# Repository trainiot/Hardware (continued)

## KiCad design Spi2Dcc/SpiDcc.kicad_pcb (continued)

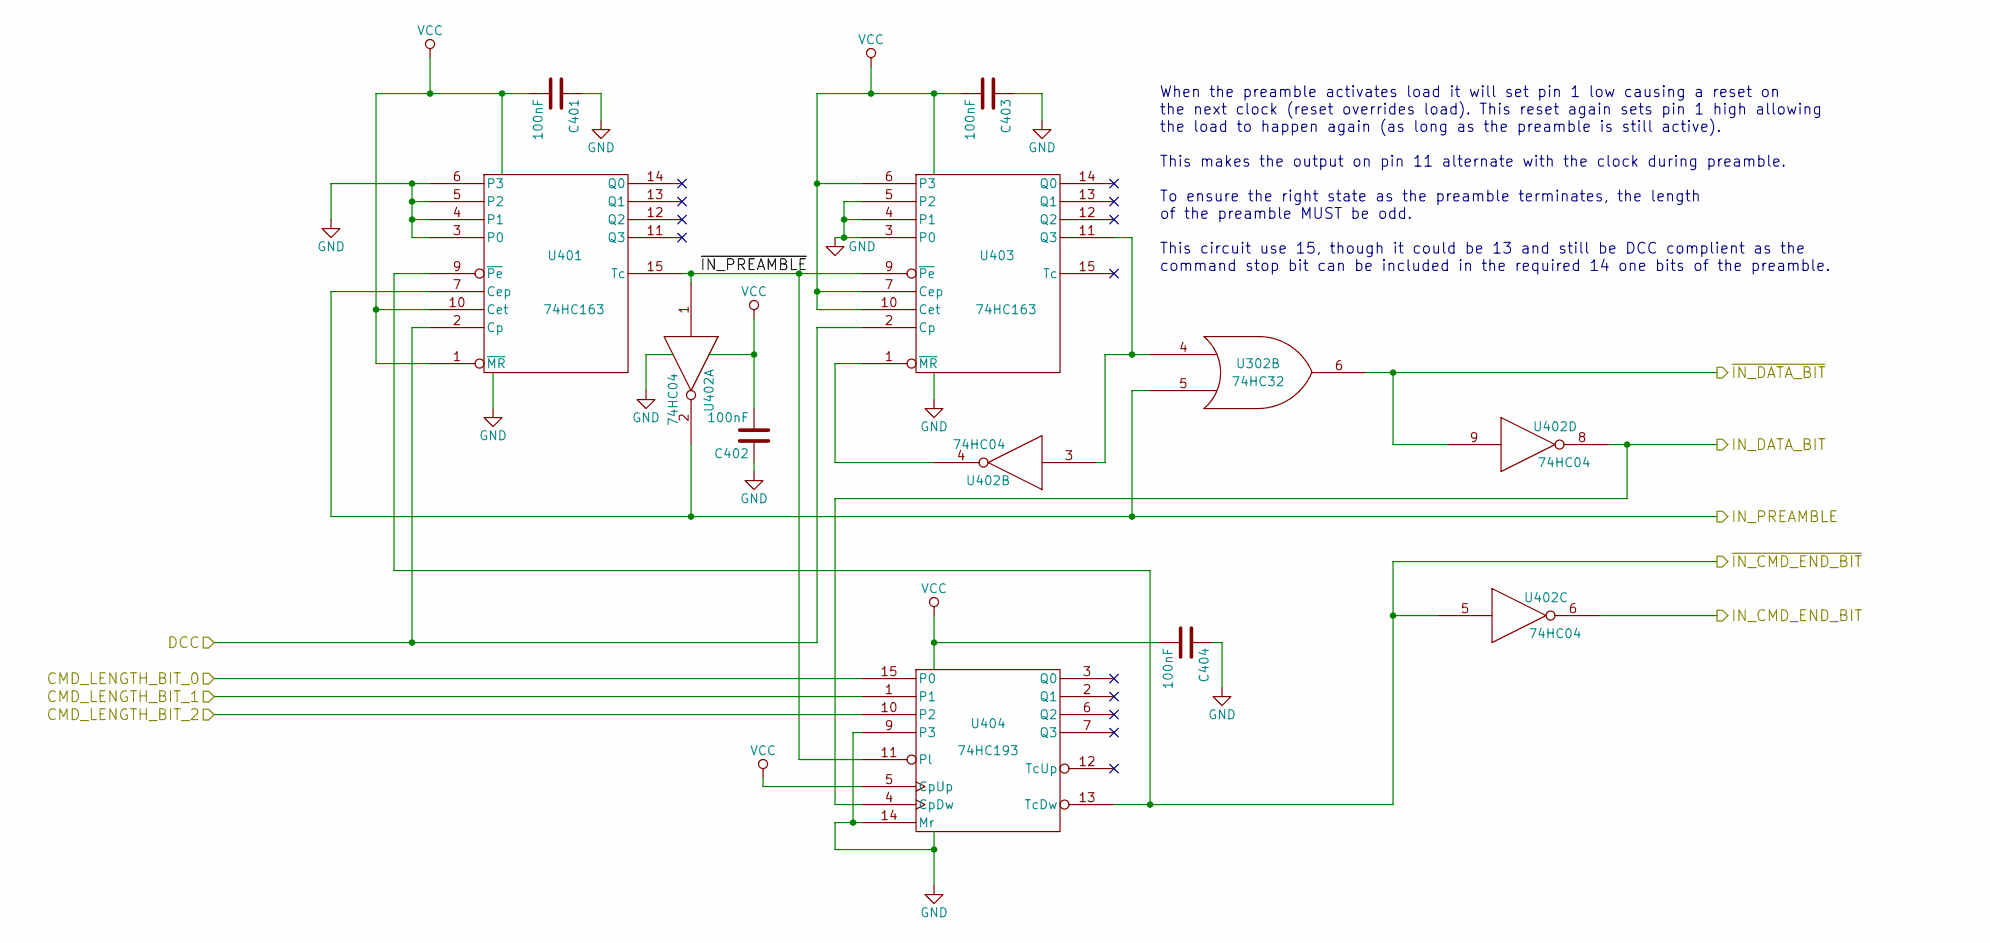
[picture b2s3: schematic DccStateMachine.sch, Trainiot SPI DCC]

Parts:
C401, C402, C403, C404: 100nF; C_0603
U302: 74HC32; SOIC-14_N
U401, U403: 74HC163; SO-16-N
U402: 74HC04; SOIC-14_N
U404: 74HC193; SO-16-N

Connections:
/Booster Connectors/DCC: U401.2 (Cp), U403.2 (Cp); also elsewhere on the board
/Command Register/CMD_LENGTH_BIT_0: U404.15 (P0); also elsewhere on the board
/Command Register/CMD_LENGTH_BIT_1: U404.1; also elsewhere on the board
/Command Register/CMD_LENGTH_BIT_2: U404.10 (P2); also elsewhere on the board
/Command Register/IN_CMD_END_BIT: U402.6; also elsewhere on the board
/Command Register/~IN_CMD_END_BIT~: U401.9 (~Pe), U402.5, U404.13 (TcDw); also elsewhere on the board
/Command Register/~IN_DATA_BIT~: U302.6, U402.9; also elsewhere on the board
/DCC Generator/IN_DATA_BIT: U402.8, U404.4 (CpDw); also elsewhere on the board
/DCC Generator/IN_PREAMBLE: U302.5, U401.7 (Cep), U402.2; also elsewhere on the board
/DCC State Machine/~IN_PREAMBLE~: U401.15 (Tc), U402.1, U403.9 (~Pe), U404.11 (Pl)
GND: C401.1, C402.1, C403.1, C404.1, U302.7 (GND), U401.3 (P0), U401.4 (P1), U401.5 (P2), U401.6 (P3), U401.8 (GND), U402.7 (GND), U403.3 (P0), U403.4 (P1), U403.5 (P2), U403.8 (GND), U404.8 (GND), U404.9 (P3), U404.14 (Mr); also elsewhere on the board
unnamed: U302.4, U402.3, U403.11 (Q3)
unnamed: U402.4, U403.1 (~MR)
VCC: C401.2, C402.2, C403.2, C404.2, U302.14 (VCC), U401.1 (~MR), U401.10 (Cet), U401.16 (VCC), U402.14 (VCC), U403.6 (P3), U403.7 (Cep), U403.10 (Cet), U403.16 (VCC), U404.5 (CpUp), U404.16 (VCC); also elsewhere on the board

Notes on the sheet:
When the preamble activates load it will set pin 1 low causing a reset on the next clock (reset overrides load). This reset again sets pin 1 high allowing the load to happen again (as long as the preamble is still active). This makes the output on pin 11 alternate with the clock during preamble. To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

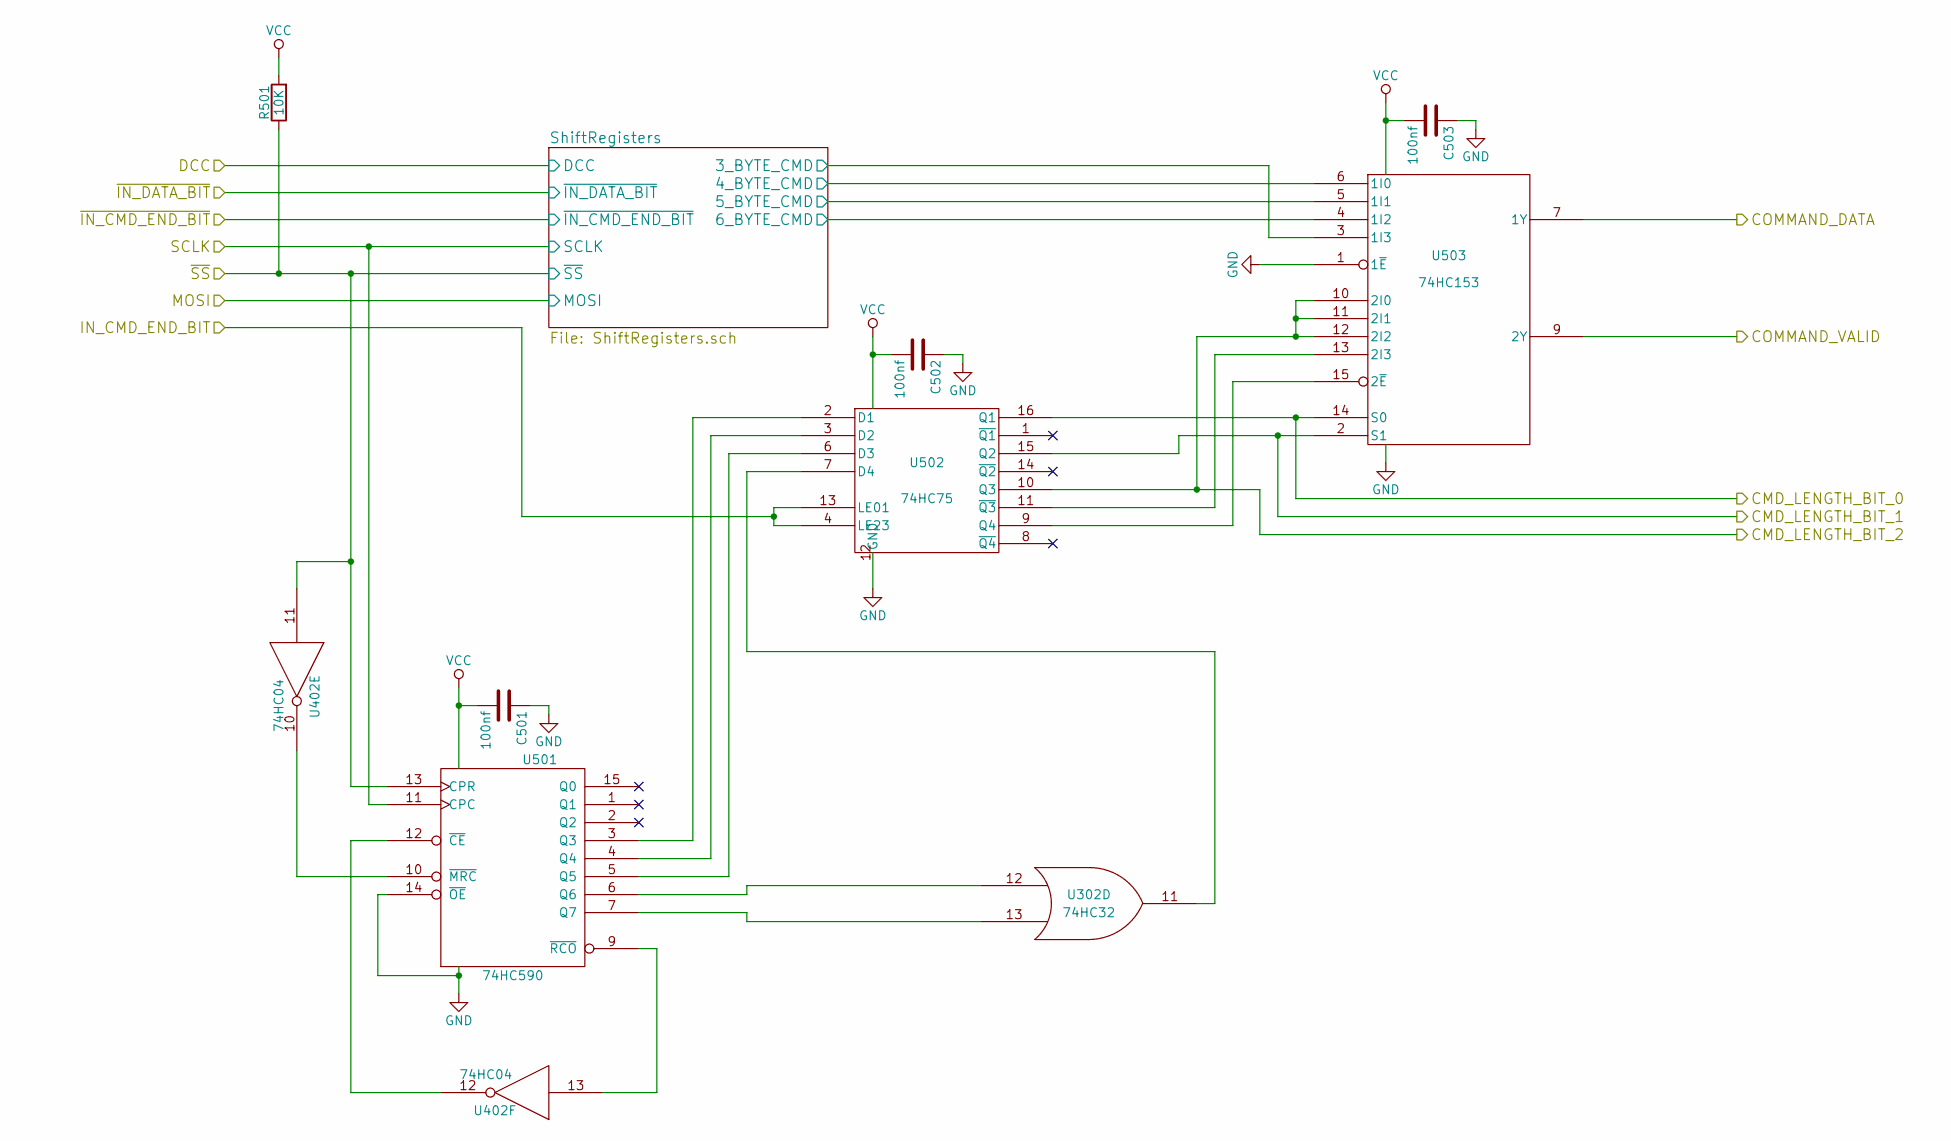
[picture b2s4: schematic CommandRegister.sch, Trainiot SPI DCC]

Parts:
C501, C502, C503: 100nf; C_0603
R501: 10K; R_0603
U302: 74HC32; SOIC-14_N
U402: 74HC04; SOIC-14_N
U501: 74HC590; SO-16-N
U502: 74HC75; SO-16-N
U503: 74HC153; SO-16-N

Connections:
/Command Register/CMD_LENGTH_BIT_0: U502.16 (Q1), U503.14 (S0); also elsewhere on the board
/Command Register/CMD_LENGTH_BIT_1: U502.15 (Q2), U503.2 (S1); also elsewhere on the board
/Command Register/CMD_LENGTH_BIT_2: U502.10 (Q3), U503.10 (2I0), U503.11 (2I1), U503.12 (2I2); also elsewhere on the board
/Command Register/COMMAND_DATA: U503.7 (1Y); also elsewhere on the board
/Command Register/COMMAND_VALID: U503.9 (2Y); also elsewhere on the board
/Command Register/IN_CMD_END_BIT: U502.4 (LE23), U502.13 (LE01); also elsewhere on the board
/Command Register/SCLK: U501.11 (CPC); also elsewhere on the board
/Command Register/ShiftRegisters/3_BYTE_CMD: U503.3 (1I3); also elsewhere on the board
/Command Register/ShiftRegisters/4_BYTE_CMD: U503.6 (1I0); also elsewhere on the board
/Command Register/ShiftRegisters/5_BYTE_CMD: U503.5 (1I1); also elsewhere on the board
/Command Register/ShiftRegisters/6_BYTE_CMD: U503.4 (1I2); also elsewhere on the board
/Command Register/~SS~: R501.1, U402.11, U501.13 (CPR); also elsewhere on the board
GND: C501.1, C502.1, C503.1, U302.7 (GND), U402.7 (GND), U501.8 (GND), U501.14 (~OE), U502.12 (GND), U503.1 (1~E~), U503.8 (GND); also elsewhere on the board
unnamed: U302.11, U502.7 (D4)
unnamed: U302.12, U501.6 (Q6)
unnamed: U302.13, U501.7 (Q7)
unnamed: U402.10, U501.10 (~MRC)
unnamed: U402.12, U501.12 (~CE)
unnamed: U402.13, U501.9 (~RCO)
unnamed: U501.3 (Q3), U502.2 (D1)
unnamed: U501.4 (Q4), U502.3 (D2)
unnamed: U501.5 (Q5), U502.6 (D3)
unnamed: U502.9 (Q4), U503.15 (2~E~)
unnamed: U502.11 (~Q3), U503.13 (2I3)
VCC: C501.2, C502.2, C503.2, R501.2, U302.14 (VCC), U402.14 (VCC), U501.16 (VCC), U502.5 (VCC), U503.16 (VCC); also elsewhere on the board

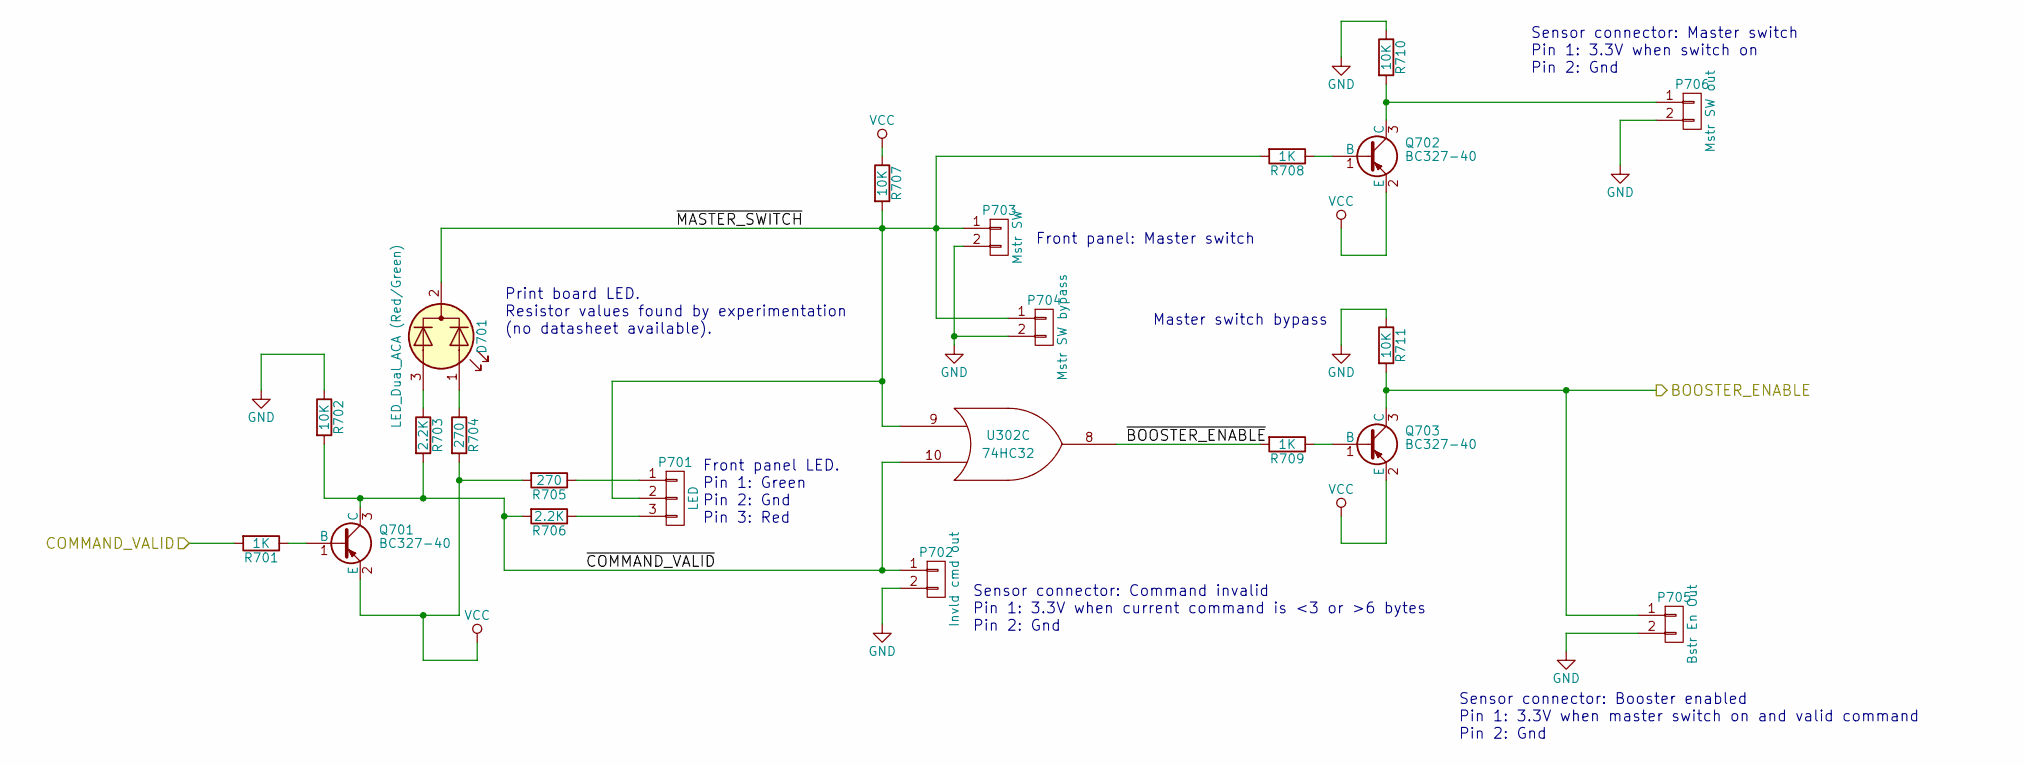
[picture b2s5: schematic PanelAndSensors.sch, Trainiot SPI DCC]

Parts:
D701: LED_Dual_ACA (Red/Green); LED_D3.0mm-3
P701: LED; JST_XH_B03B-XH-A_03x2.50mm_Straight
P702: Invld cmd out; JST_XH_B02B-XH-A_02x2.50mm_Straight
P703: Mstr SW; JST_XH_B02B-XH-A_02x2.50mm_Straight
P704: Mstr SW bypass; Pin_Header_Straight_1x02_Pitch2.54mm
P705: Bstr En Out; JST_XH_B02B-XH-A_02x2.50mm_Straight
P706: Mstr SW out; JST_XH_B02B-XH-A_02x2.50mm_Straight
Q701, Q702, Q703: BC327-40; SOT-23
R701, R708, R709: 1K; R_0603
R702, R707, R710, R711: 10K; R_0603
R703, R706: 2.2K; R_0603
R704, R705: 270; R_0603
U302: 74HC32; SOIC-14_N

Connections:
/Booster Connectors/BOOSTER_ENABLE: P705.1, Q703.3 (C), R711.2; also elsewhere on the board
/Command Register/COMMAND_VALID: R701.2; also elsewhere on the board
/Panel and Sensors/~BOOSTER_ENABLE: R709.2, U302.8
/Panel and Sensors/~COMMAND_VALID: P702.1, Q701.3 (C), R702.2, R703.2, R706.2, U302.10
/Panel and Sensors/~MASTER_SWITCH: D701.2 (K), P701.2, P703.1, P704.1, R707.2, R708.2, U302.9
GND: P702.2, P703.2, P704.2, P705.2, P706.2, R702.1, R710.1, R711.1, U302.7 (GND); also elsewhere on the board
unnamed: D701.1 (A1), R704.1
unnamed: D701.3 (A2), R703.1
unnamed: P701.1, R705.1
unnamed: P701.3, R706.1
unnamed: P706.1, Q702.3 (C), R710.2
unnamed: Q701.1 (B), R701.1
unnamed: Q702.1 (B), R708.1
unnamed: Q703.1 (B), R709.1
VCC: Q701.2 (E), Q702.2 (E), Q703.2 (E), R704.2, R705.2, R707.1, U302.14 (VCC); also elsewhere on the board

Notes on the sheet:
Print board LED. Resistor values found by experimentation (no datasheet available).
Front panel LED. Pin 1: Green Pin 2: Gnd Pin 3: Red
Sensor connector: Booster enabled Pin 1: 3.3V when master switch on and valid command Pin 2: Gnd
Sensor connector: Master switch Pin 1: 3.3V when switch on Pin 2: Gnd
Sensor connector: Command invalid Pin 1: 3.3V when current command is <3 or >6 bytes Pin 2: Gnd
Front panel: Master switch
Master switch bypass

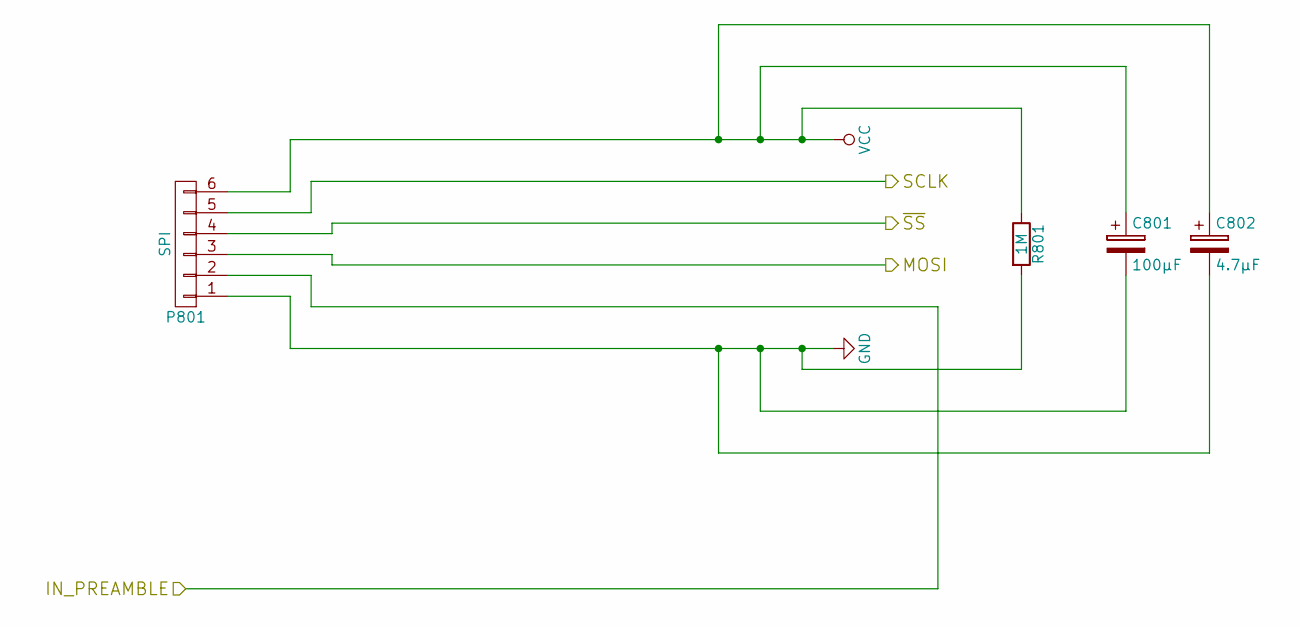
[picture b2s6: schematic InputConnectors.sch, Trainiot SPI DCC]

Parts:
C801: 100μF; CP_Radial_D6.3mm_P2.50mm
C802: 4.7μF; CP_Radial_D5.0mm_P2.00mm
P801: SPI; JST_XH_B06B-XH-A_06x2.50mm_Straight
R801: 1M; R_0603

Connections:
/Command Register/MOSI: P801.3; also elsewhere on the board
/Command Register/SCLK: P801.5; also elsewhere on the board
/Command Register/~SS~: P801.4; also elsewhere on the board
/DCC Generator/IN_PREAMBLE: P801.2; also elsewhere on the board
GND: C801.2, C802.2, P801.1, R801.2; also elsewhere on the board
VCC: C801.1, C802.1, P801.6, R801.1; also elsewhere on the board

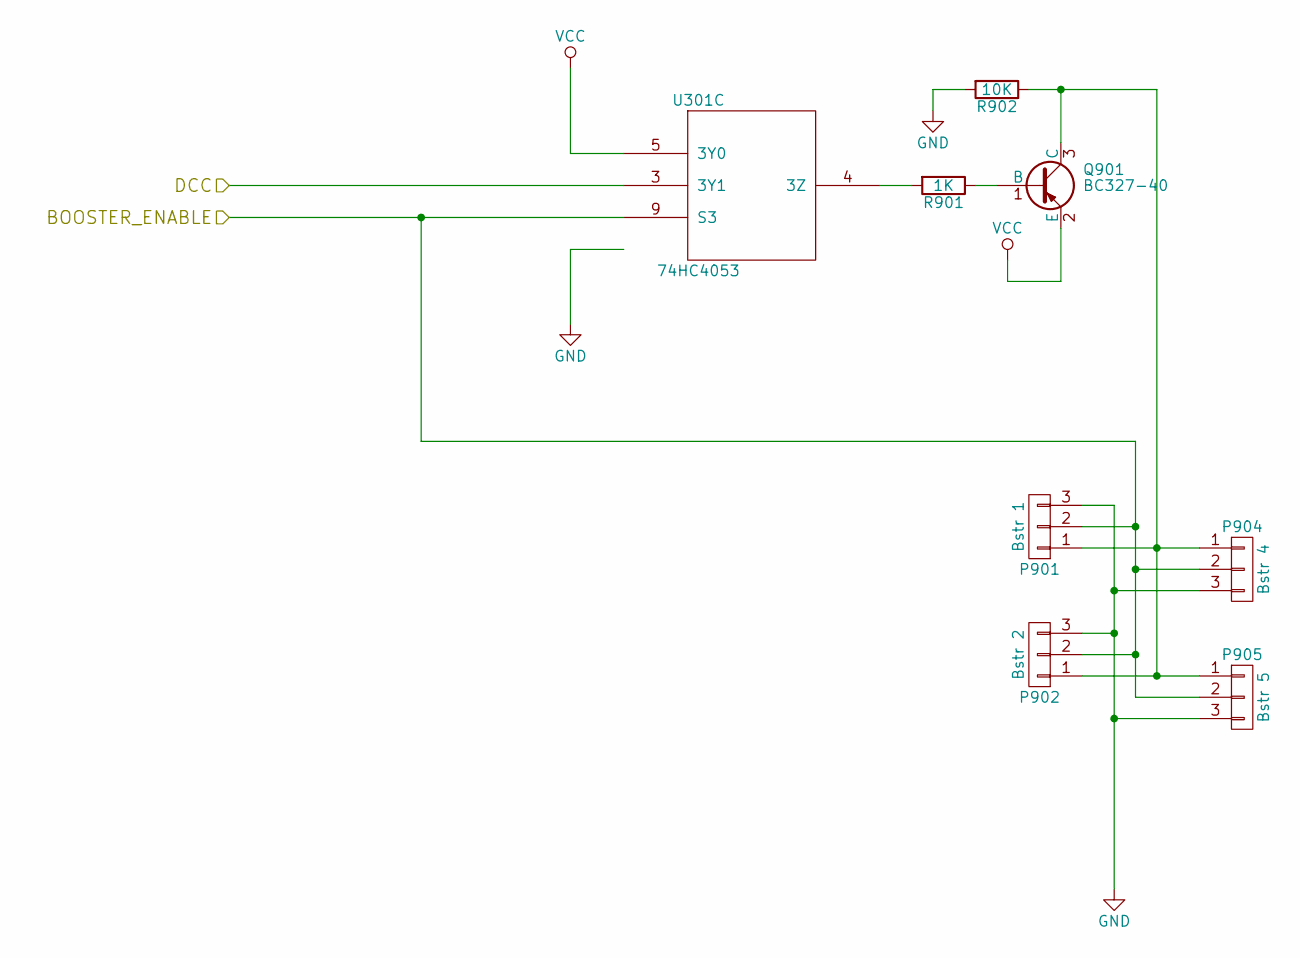
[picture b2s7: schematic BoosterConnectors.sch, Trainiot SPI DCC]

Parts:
P901: Bstr 1; JST_XH_B03B-XH-A_03x2.50mm_Straight
P902: Bstr 2; JST_XH_B03B-XH-A_03x2.50mm_Straight
P904: Bstr 4; JST_XH_B03B-XH-A_03x2.50mm_Straight
P905: Bstr 5; JST_XH_B03B-XH-A_03x2.50mm_Straight
Q901: BC327-40; SOT-23
R901: 1K; R_0603
R902: 10K; R_0603
U301: 74HC4053; SO-16-N

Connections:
/Booster Connectors/BOOSTER_ENABLE: P901.2, P902.2, P904.2, P905.2, U301.9 (S3); also elsewhere on the board
/Booster Connectors/DCC: U301.3 (3Y1); also elsewhere on the board
GND: P901.3, P902.3, P904.3, P905.3, R902.2, U301.6 (E), U301.7 (VEE), U301.8 (GND); also elsewhere on the board
unnamed 33: P901.1, P902.1, P904.1, P905.1, Q901.3 (C), R902.1; also elsewhere on the board
unnamed: Q901.1 (B), R901.1
unnamed: R901.2, U301.4 (3Z)
VCC: Q901.2 (E), U301.5 (3Y0), U301.16 (VDD); also elsewhere on the board

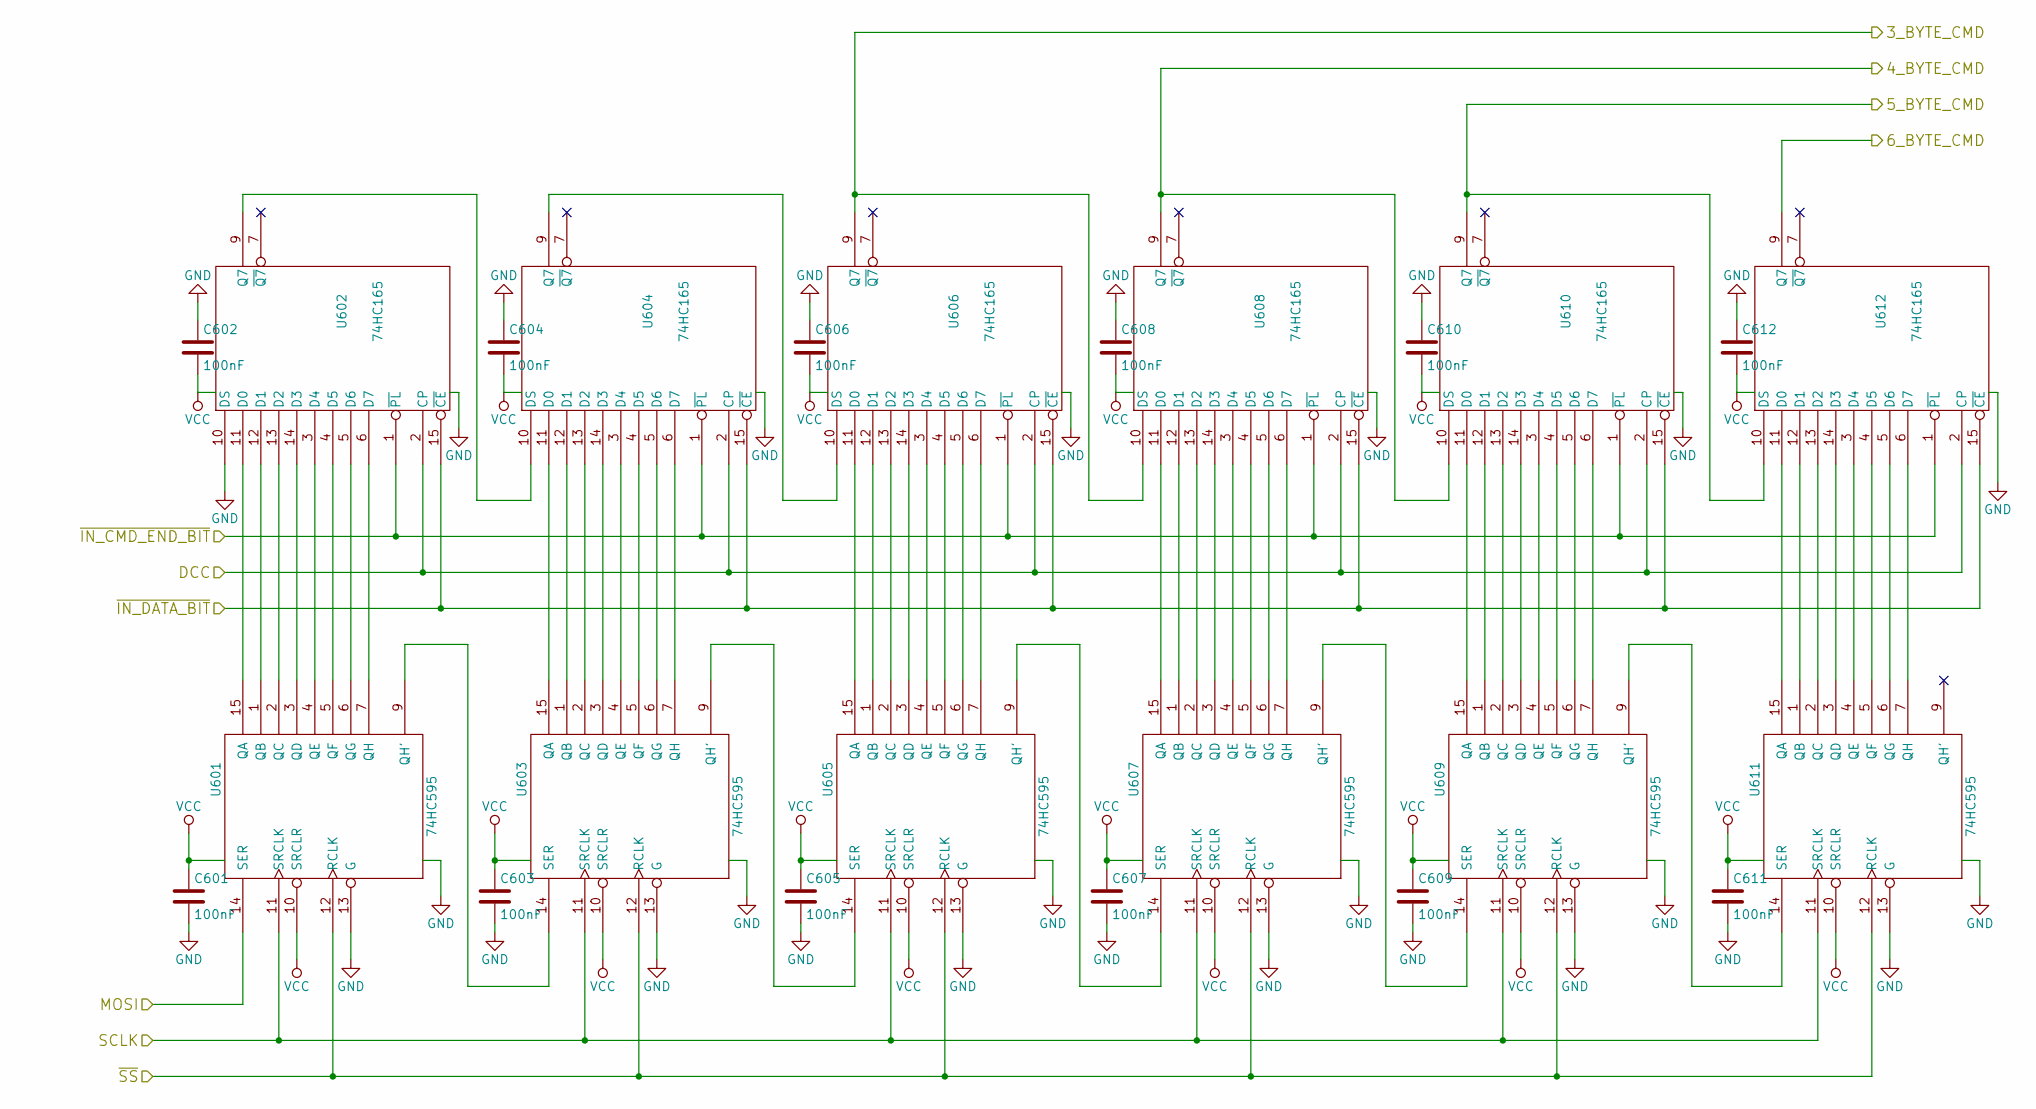
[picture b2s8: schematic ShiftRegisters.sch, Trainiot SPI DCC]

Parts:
C601, C602, C603, C604, C605, C606, C607, C608, C609, C610, C611, C612: 100nF; C_0603
U601, U603, U605, U607, U609, U611: 74HC595; SO-16-N
U602, U604, U606, U608, U610, U612: 74HC165; SO-16-N

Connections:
/Booster Connectors/DCC: U602.2 (CP), U604.2 (CP), U606.2 (CP), U608.2 (CP), U610.2 (CP), U612.2 (CP); also elsewhere on the board
/Command Register/MOSI: U601.14 (SER); also elsewhere on the board
/Command Register/SCLK: U601.11 (SRCLK), U603.11 (SRCLK), U605.11 (SRCLK), U607.11 (SRCLK), U609.11 (SRCLK), U611.11 (SRCLK); also elsewhere on the board
/Command Register/ShiftRegisters/3_BYTE_CMD: U606.9 (Q7), U608.10 (DS); also elsewhere on the board
/Command Register/ShiftRegisters/4_BYTE_CMD: U608.9 (Q7), U610.10 (DS); also elsewhere on the board
/Command Register/ShiftRegisters/5_BYTE_CMD: U610.9 (Q7), U612.10 (DS); also elsewhere on the board
/Command Register/ShiftRegisters/6_BYTE_CMD: U612.9 (Q7); also elsewhere on the board
/Command Register/~IN_CMD_END_BIT~: U602.1 (~PL), U604.1 (~PL), U606.1 (~PL), U608.1 (~PL), U610.1 (~PL), U612.1 (~PL); also elsewhere on the board
/Command Register/~IN_DATA_BIT~: U602.15 (~CE), U604.15 (~CE), U606.15 (~CE), U608.15 (~CE), U610.15 (~CE), U612.15 (~CE); also elsewhere on the board
/Command Register/~SS~: U601.12 (RCLK), U603.12 (RCLK), U605.12 (RCLK), U607.12 (RCLK), U609.12 (RCLK), U611.12 (RCLK); also elsewhere on the board
GND: C601.2, C602.1, C603.2, C604.1, C605.2, C606.1, C607.2, C608.1, C609.2, C610.1, C611.2, C612.1, U601.8 (GND), U601.13 (G), U602.8 (GND), U602.10 (DS), U603.8 (GND), U603.13 (G), U604.8 (GND), U605.8 (GND), U605.13 (G), U606.8 (GND), U607.8 (GND), U607.13 (G), U608.8 (GND), U609.8 (GND), U609.13 (G), U610.8 (GND), U611.8 (GND), U611.13 (G), U612.8 (GND); also elsewhere on the board
unnamed: U601.1 (QB), U602.12 (D1)
unnamed: U601.2 (QC), U602.13 (D2)
unnamed: U601.3 (QD), U602.14 (D3)
unnamed: U601.4 (QE), U602.3 (D4)
unnamed: U601.5 (QF), U602.4 (D5)
unnamed: U601.6 (QG), U602.5 (D6)
unnamed: U601.7 (QH), U602.6 (D7)
unnamed: U601.9 (QH'), U603.14 (SER)
unnamed: U601.15 (QA), U602.11 (D0)
unnamed: U602.9 (Q7), U604.10 (DS)
unnamed: U603.1 (QB), U604.12 (D1)
unnamed: U603.2 (QC), U604.13 (D2)
unnamed: U603.3 (QD), U604.14 (D3)
unnamed: U603.4 (QE), U604.3 (D4)
unnamed: U603.5 (QF), U604.4 (D5)
unnamed: U603.6 (QG), U604.5 (D6)
unnamed: U603.7 (QH), U604.6 (D7)
unnamed: U603.9 (QH'), U605.14 (SER)
unnamed: U603.15 (QA), U604.11 (D0)
unnamed: U604.9 (Q7), U606.10 (DS)
unnamed: U605.1 (QB), U606.12 (D1)
unnamed: U605.2 (QC), U606.13 (D2)
unnamed: U605.3 (QD), U606.14 (D3)
unnamed: U605.4 (QE), U606.3 (D4)
unnamed: U605.5 (QF), U606.4 (D5)
unnamed: U605.6 (QG), U606.5 (D6)
unnamed: U605.7 (QH), U606.6 (D7)
unnamed: U605.9 (QH'), U607.14 (SER)
unnamed: U605.15 (QA), U606.11 (D0)
unnamed: U607.1 (QB), U608.12 (D1)
unnamed: U607.2 (QC), U608.13 (D2)
unnamed: U607.3 (QD), U608.14 (D3)
unnamed: U607.4 (QE), U608.3 (D4)
unnamed: U607.5 (QF), U608.4 (D5)
unnamed: U607.6 (QG), U608.5 (D6)
unnamed: U607.7 (QH), U608.6 (D7)
unnamed: U607.9 (QH'), U609.14 (SER)
unnamed: U607.15 (QA), U608.11 (D0)
unnamed: U609.1 (QB), U610.12 (D1)
unnamed: U609.2 (QC), U610.13 (D2)
unnamed: U609.3 (QD), U610.14 (D3)
unnamed: U609.4 (QE), U610.3 (D4)
unnamed: U609.5 (QF), U610.4 (D5)
unnamed: U609.6 (QG), U610.5 (D6)
unnamed: U609.7 (QH), U610.6 (D7)
unnamed: U609.9 (QH'), U611.14 (SER)
unnamed: U609.15 (QA), U610.11 (D0)
unnamed: U611.1 (QB), U612.12 (D1)
unnamed: U611.2 (QC), U612.13 (D2)
unnamed: U611.3 (QD), U612.14 (D3)
unnamed: U611.4 (QE), U612.3 (D4)
unnamed: U611.5 (QF), U612.4 (D5)
unnamed: U611.6 (QG), U612.5 (D6)
unnamed: U611.7 (QH), U612.6 (D7)
unnamed: U611.15 (QA), U612.11 (D0)
VCC: C601.1, C602.2, C603.1, C604.2, C605.1, C606.2, C607.1, C608.2, C609.1, C610.2, C611.1, C612.2, U601.10 (SRCLR), U601.16 (VCC), U602.16 (VCC), U603.10 (SRCLR), U603.16 (VCC), U604.16 (VCC), U605.10 (SRCLR), U605.16 (VCC), U606.16 (VCC), U607.10 (SRCLR), U607.16 (VCC), U608.16 (VCC), U609.10 (SRCLR), U609.16 (VCC), U610.16 (VCC), U611.10 (SRCLR), U611.16 (VCC), U612.16 (VCC); also elsewhere on the board

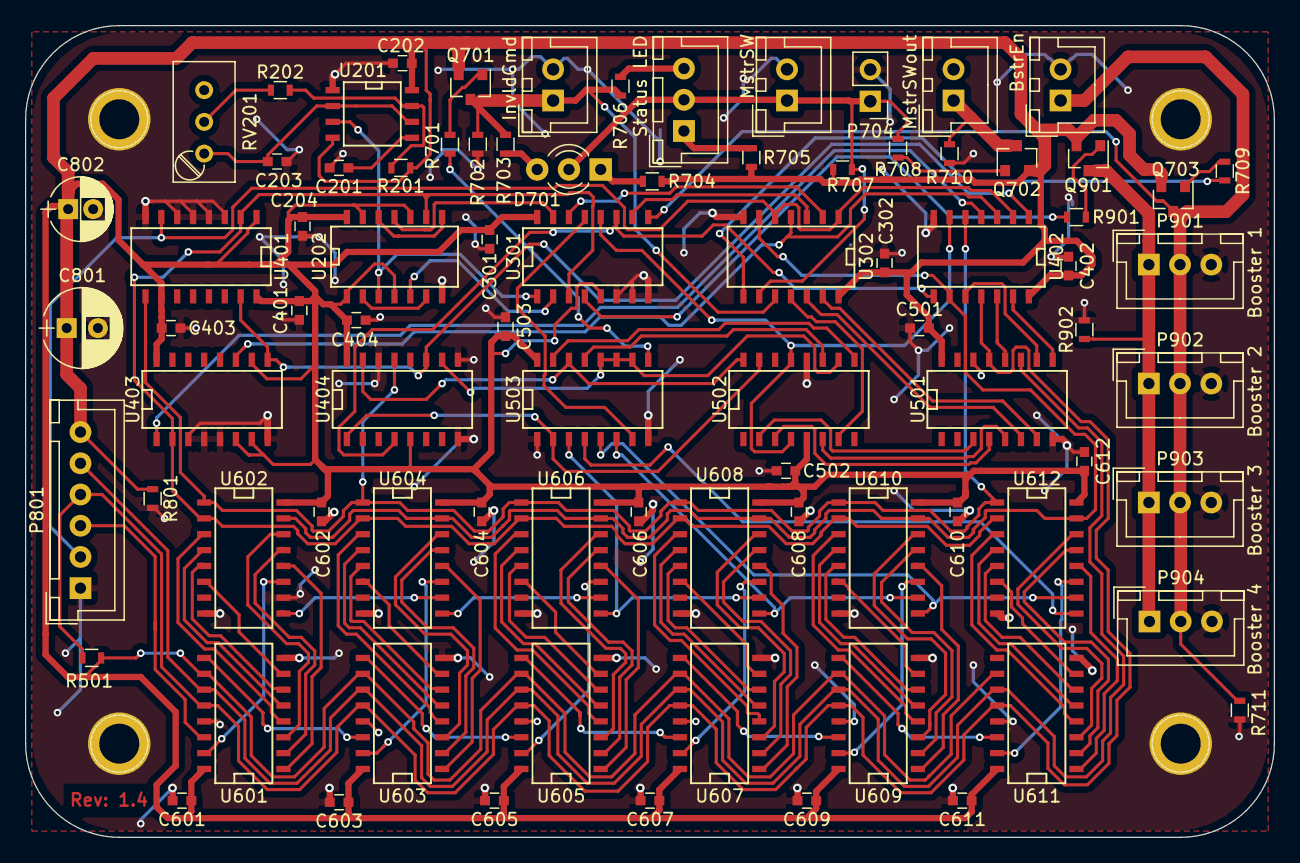
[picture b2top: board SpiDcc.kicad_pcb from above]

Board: 2 copper layers, 100.0 x 65.0 mm, 84 parts (0 on the bottom side), 115 nets.

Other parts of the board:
P903: Bstr 3; JST_XH_B03B-XH-A_03x2.50mm_Straight

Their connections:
/Booster Connectors/BOOSTER_ENABLE: P903.2; also elsewhere on the board
GND: P903.3; also elsewhere on the board
unnamed 33: P903.1; also elsewhere on the board

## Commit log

2017-03-30 v1.3 initial checkin - earlier development was done without proper revision control (yes, I know)....
2017-03-30 Set solder mask clearance and minimum width as specified by Elecrow to 0.2
2017-03-30 Updated revision date (revision number not updated as no prior version was published)
2017-03-30 Changing the solder mask settings again - based on recommendation found here: http://www.360customs.de/en/2017/01/kicad-elecrow-pcb-service/
2017-03-30 Gerber files as send for production (except names where changed to match Elecrow naming requirements).
2017-03-30 Missing dcm file for the library - forgotten on first check in.
2017-03-31 Added missing SpiDcc-cache.lib file - including it makes it possible to open the schema without having the exact same libraries that where used when creating the schema.
2017-03-31 Exclude eeschema backup files.
2017-04-24 Started to document the circuit
    Initial checkin just to make sure nothing is lost. Yes, this should be on a separate branch in theory, but it adds value right away so this will do.
2017-04-24 Documented shift registers.
2017-04-24 Documented the clock generator.
2017-04-24 Documented DCC State Machine
2017-04-24 Documented DCC generator
2017-04-24 Documented Panel and Sensors
2017-04-24 Documented booster connections
    This finishes the first pass of the circuit documentation. There is still a TODO or two, and a lot more detail and proofreading would certainly be beneficial - but then, a lot of things would be bene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
2017-04-25 Force image reload correct multiline notes.
2017-04-26 Fixed missing connection from U404 to VCC in DccStateMachine schematic. Schematic revision updated to 1.4, pcb not yet.
2017-04-26 Added NoConnect to unconnected pins
2017-04-26 Removed haching hack for KiCadDoxer links
    As KiCadDoxer now set the right caching headers
2017-04-26 Added NoConnect
2017-04-27 Changed back to rev 1.3, update made to 1.4 was invalid.
2017-05-15 Delete LedStatusLight.sch
    Functionality was moved to PanelAndSensors.sch but the original file was not deleted.
2017-10-16 Added SN754410 to component library.
2017-10-16 Created empty booster project and configured it to use the component library.
2017-10-18 Minimalistic but functional booster (no reverser, no overcurrent protection, no output LED, ...)
2017-10-19 Fixed missing pull-up on 6n137 optocoupler driving the DCC signal. Moved power, DCC input and track output to separate sheets.
2017-10-22 Fixed pull down to the required pull-up on the 6N137.
2017-10-22 Renamed track output to driver as the overcurrent protection should still be added.
2017-10-22 First draft of detecting overcurrent.
2017-10-25 Somewhat optimistic circuit to add delay to overcurrent sensing and release.
2017-10-28 Trim pots to comparitors now set up to use fewer resistors. Added status sheet, currently not doing anything useful.
2017-11-05 Working on replacing over current detection to overcurrent protection.
2017-11-12 Over current protection and detection - with detection delay and release delay.
2017-11-12 Added reversing support. Working on status output.
2017-11-13 Added initial logic to the status. Still need to hook up LED, validate, and optimize for fewer gates if possible.
2017-11-17 Getting close to feature complete for a single channel.
2017-11-18 Added meassurement tabs and other general "finalizing touches"
2017-11-18 Added schematic for 3 x SPST switch.
2017-11-19 Reference voltage of reverser is now the 1V after the resistor dropper. This allows running one wire less to the sensor unit, at the cost of the photo resistor only working off 1V.
2017-11-19 Added DCC Enable inverter. Primarely to allow meassuring track voltage easily - by enabling output with no DCC signal giving a steady 12V on the track. Replaced AND gates with NAND to free up the nec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
2017-11-19 Removed redundant work in text node.
2017-11-20 Use actual test point instead of 1 pin jumpers.
2017-11-27 Minor fixes based on breadboard experiments.
2017-12-17 Kind of working with the overcurrent retry, but not liking the RC delay in the final output to the motor driver.
2017-12-17 Added 555 timer to control overcurrent release delay. Simpler to control as turning the power off cleared the overflow before the capacitor controlling the release delay was fully cleared. The LM339 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
2017-12-17 Hooking up reset of overcurrent to DCC Enable. Most likely going to change it to the master switch instead (detecting both would be nice, but probably not worth introducing yet another IC for).
2017-12-18 Reset overcurrent timeout now linked to the master switch, not the input signal.
2017-12-18 Changed transistor driving reversing indicator LED to NPN to get it to light up when reversing, not light up when not reversing.
2017-12-19 Removed need for enable signal replacing it with a missing pulse detection RC based circuit.
2017-12-19 Using spare xor gate to make all transistors PNP types.
2017-12-19 Fixed missing connections.
2017-12-19 Fixed optocoupler circuit - had been reading the wrong datasheet :) Still need to invert the pulse detector op amp and adjust reference voltage as the optocoupler inverse the signal.
2017-12-21 Pulse detector circuit included.
2017-12-23 Various adjustments based on breadboard prototype.
2017-12-23 Changed to SMD components. Train is now moving. :)
2017-12-24 Replaced NAND gate with AND as the additional NOT gates ended up only used to negate the NAND gates directly. One extra AND gate used to allow resetting overcurrent by either master switch or DCC dis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
2017-12-24 Annotation, fix missing connection.
2017-12-26 Assigned footprints & minor adjustments.
2017-12-26 Added footprint for LM338 with heatshield
2017-12-26 Started working on the PCB layout. Just getting a rough idea for now.
2017-12-28 Still working on PCB layout
2017-12-28 Starting to add traces. Minor schematic changes to aid routing.
2017-12-29 First full layout pass of the PCB.
2017-12-30 Made board slightly larger to have more space along the edge. It is now 9.7 x 6 cm
2017-12-30 Minor adjustments to traces
2017-12-30 Added gnd plane, starting to hook up gnd pads.
2017-12-30 More ground connections and other traces added. Still need to reposition R609.
2017-12-31 Further trace optimizations and fixed a few missing connections.
2017-12-31 Fixed track clearance (one DRC validation fail as well as a few tracks unnecessary close to through whole components.
2017-12-31 Starting to add description text to connectors.
2017-12-31 Misc adjustments. Added text to all connectors.
2017-12-31 Increased spacing between connectors. Various trace optimizations.
2017-12-31 Added logos and various cleanup of traces/via positions.
2017-12-31 Minor adjustment
2018-01-01 Turns out last minor adjustment was actually an error. :)
2018-01-01 Move U604 reference so it no longer overlaps
2018-01-01 Increased drill size of the heatshield.
2018-01-01 Increased spacing for a trace to throughhole pad
2018-01-01 Updated ground polygon
2018-01-01 Adding gerber files, just on case they turn out to be useful somehow.
2018-01-01 Fixed resistor value.
2018-01-02 Initial design of the multiplexer and SPI input. Still need to find a way to create the grid.
2018-01-03 Added sensor grid schematics.
2018-01-03 Addel labels to the wires in the sensor grid.
2018-01-03 Added sensor wire labels
2018-01-03 Adding a sheet for data capture (ADC)
2018-01-03 Made library path relative.
2018-01-04 Added byte start pulse generator
2018-01-04 Added TLC5510 ADC with reference circuit on the power supply rails.
2018-01-13 Increased resistor sizes on opt couplers and LED's to ensure the 78L05 can deliver enough power.
2018-01-13 Working on adding analog part with SPI adjustment so the computer can control the opamps without needing manual trimpots.
2018-01-18 Working on the analog input.
2018-01-19 Changed booster reversed polarity protection from a diode to a p channel mosfet to reduce the voltage drop.
2018-01-19 Increased trace width on a (very short) 5V power rail.
2018-01-19 Added missing text labels for switches.
2018-01-19 Increased size of grounded mounting pads and connected them to the ground plane without a thermal pad.
2018-02-01 Working on new connector grid.
2018-02-08 Fixed 7805 ->7805
2018-02-08 fix command length bits swapped. Connect mounting hole pads to GND.
2018-03-11 Starting to prototype matrix connectors.
2018-03-11 Fixed DCC input direction through optocoupler reversed.
2018-04-25 Created new project.
2018-04-26 Analog input first attempt, working on the SPI input driving the address.
2018-04-29 Introduced the analog input selector.
2018-05-03 Added initial analog input.
2018-05-14 Redesigned S88, redesigned power, started to change all ESP32 pin allocations.
2018-05-17 Updated analog input path to be more flexible in amplification
2018-05-17 Added XPRESS net pins on the ESP32. Still looking for a way to control input address
2018-05-19 Added USB connection
2018-05-19 Added UART header to allow programming without adding USB support (cheaper, less soldering)
2018-05-19 Added 5V pin to the UART programming interface to allow powering from an USB adapter easily.
2018-05-19 Added missing sym lib table.
2018-05-20 Added ethernet
2018-05-20 Added pull up to shift register output for S88
2018-05-20 Working on adding LocoNet
2018-05-20 Added LocoNet
2018-05-21 Added xpressnet and GPIO. Rearranged schematic to fit in A1.
2018-05-21 Minor rearrangement of GPIO pins.
2018-05-21 Changed reference voltages in the inputs to avoid having 5V mandatory. Added a pull up instead. Not sure how usefull it will be, but I do not really need the extra input.
2018-06-04 Removed GPIO pins. Used the pins to eliminate SPI in (MOSI). Rearranged SPI pins to the native pins so they can bypass the matrix.
2018-08-19 Added missing ground to 1117 3v3. Updated to KiCad 5.
2018-11-30 Redesigned power/attenuation to no longer require a negative rail at the cost of possible minor current feedback to sensor.
2018-12-01 Initial foot print assigments
2018-12-02 Updated diodes to SMD
